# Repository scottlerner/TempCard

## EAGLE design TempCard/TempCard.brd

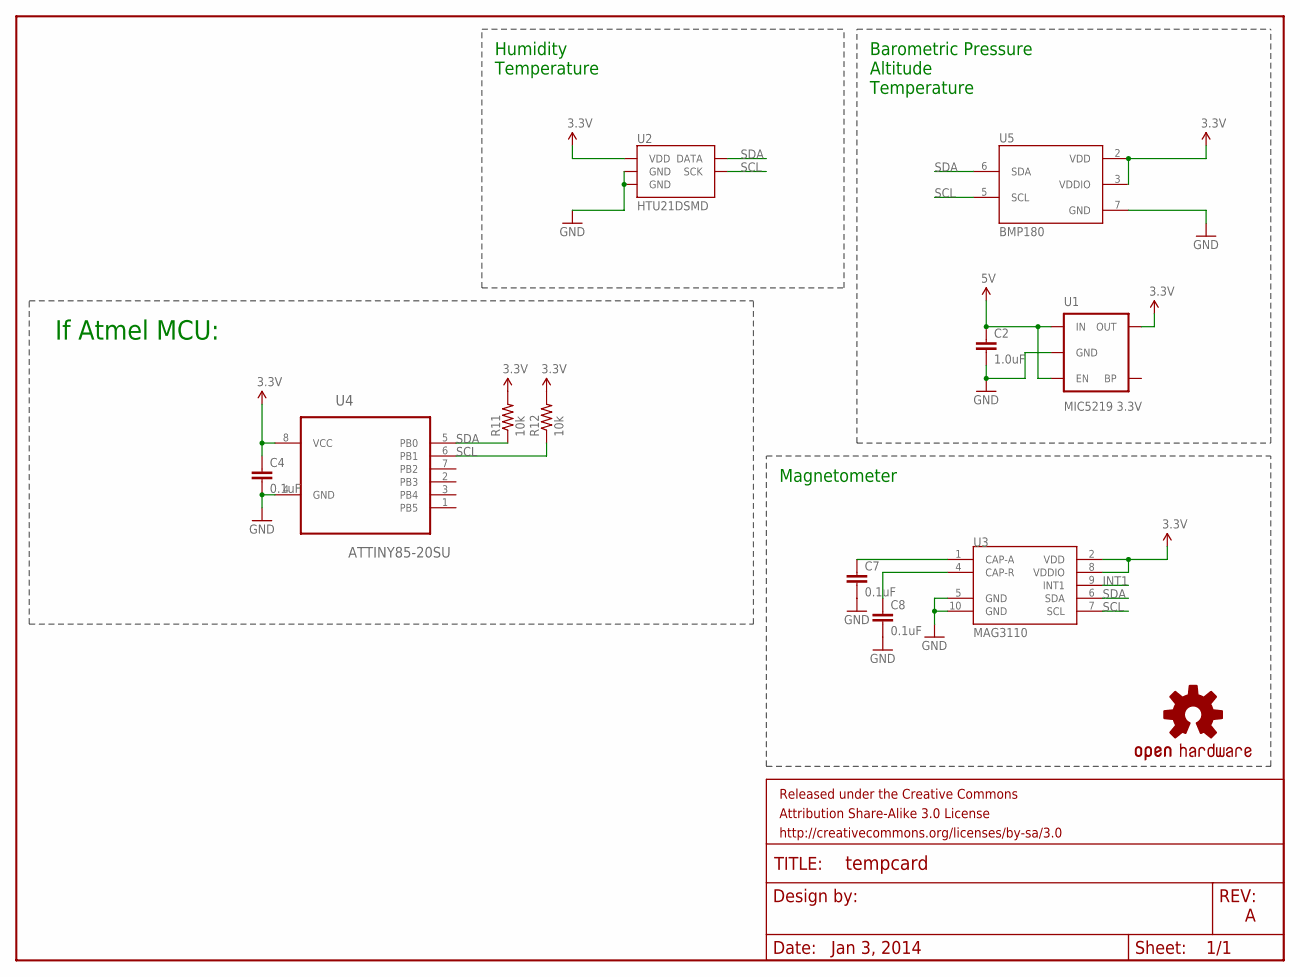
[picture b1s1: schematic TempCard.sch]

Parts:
C2: 1.0uF; 0805
C4: 0.1uF; 0805
C7, C8: 0.1uF; 0402-CAP
FRAME1: FRAME-LETTER; CREATIVE_COMMONS
LOGO1: OSHW-LOGOM; OSHW-LOGO-M
R11, R12: 10k; 0805
U1: MIC5219 3.3V; SOT23-5
U2: HTU21DSMD; HTU21D
U3: MAG3110; DFN-10
U4: ATTINY85-20SU; SOIC127P798X216-8N
U5: BMP180

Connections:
3.3V: C4.1, R11.2, R12.2, U1.5 (OUT), U2.VDD, U3.2 (VDD), U3.8 (VDDIO), U4.8 (VCC), U5.2 (VDD), U5.3 (VDDIO)
5V: C2.1, U1.1 (IN), U1.3 (EN)
GND: C2.2, C4.2, C7.2, C8.2, U1.2 (GND), U2.7 (GND), U2.GND, U3.5 (GND), U3.10 (GND), U4.4 (GND), U5.7 (GND)
INT1: U3.9 (INT1)
unnamed: C7.1, U3.1 (CAP-A)
unnamed: C8.1, U3.4 (CAP-R)
SCL: R12.1, U3.7 (SCL), U4.6 (PB1)
SDA: R11.1, U3.6 (SDA), U4.5 (PB0)

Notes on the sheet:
Barometric Pressure Altitude Temperature
Humidity Temperature
Jan 3, 2014
Magnetometer
If Atmel MCU:

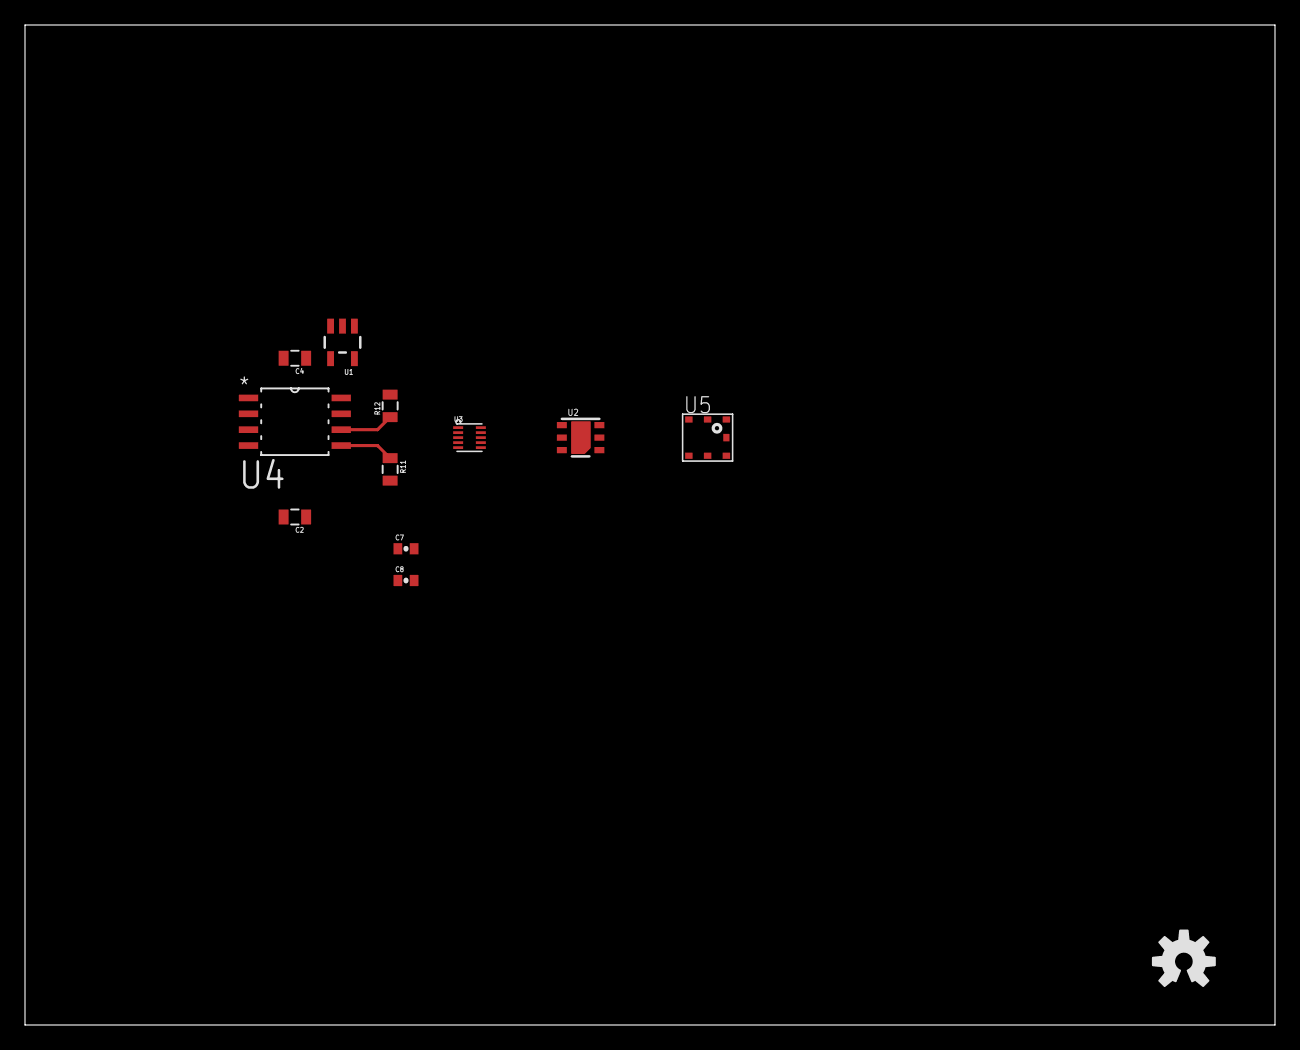
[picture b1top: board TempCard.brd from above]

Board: 2 copper layers, 100.0 x 80.0 mm, 13 parts (0 on the bottom side), 7 nets.

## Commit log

2014-01-04 Initial Eagle Files
2014-01-04 Added BMP085/180
    Added 5V to 3.3V Regulator, and circuitry for BMP085/180. Later to be
    changed to BMP180 officially.
2014-01-04 Adding sensors
    BMP085, HMC5883L, SHT15
2014-01-08 MCU/Sensor Edit
    Switched the magnetometer. Added potential MCUs for Atmel and PIC. More than likely going with ATTiny85. More testing to follow.
2014-02-09 Plane Stuff
    I don't know what exactly this changed.
2014-02-10 Final Hardware Selected
    HTU21D, MAG3110, BMP180. Still room in the future for adding LCD screen as well as other functionality in different series.

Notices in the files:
parts and their libraries:
SparkFun-Aesthetics: Licensing: CC v3.0 Share-Alike You are welcome to use this library for commercial purposes.
SparkFun-Aesthetics: Released under the Creative Commons Attribution Share-Alike 3.0 License
SparkFun-Aesthetics: http://creativecommons.org/licenses/by-sa/3.0
